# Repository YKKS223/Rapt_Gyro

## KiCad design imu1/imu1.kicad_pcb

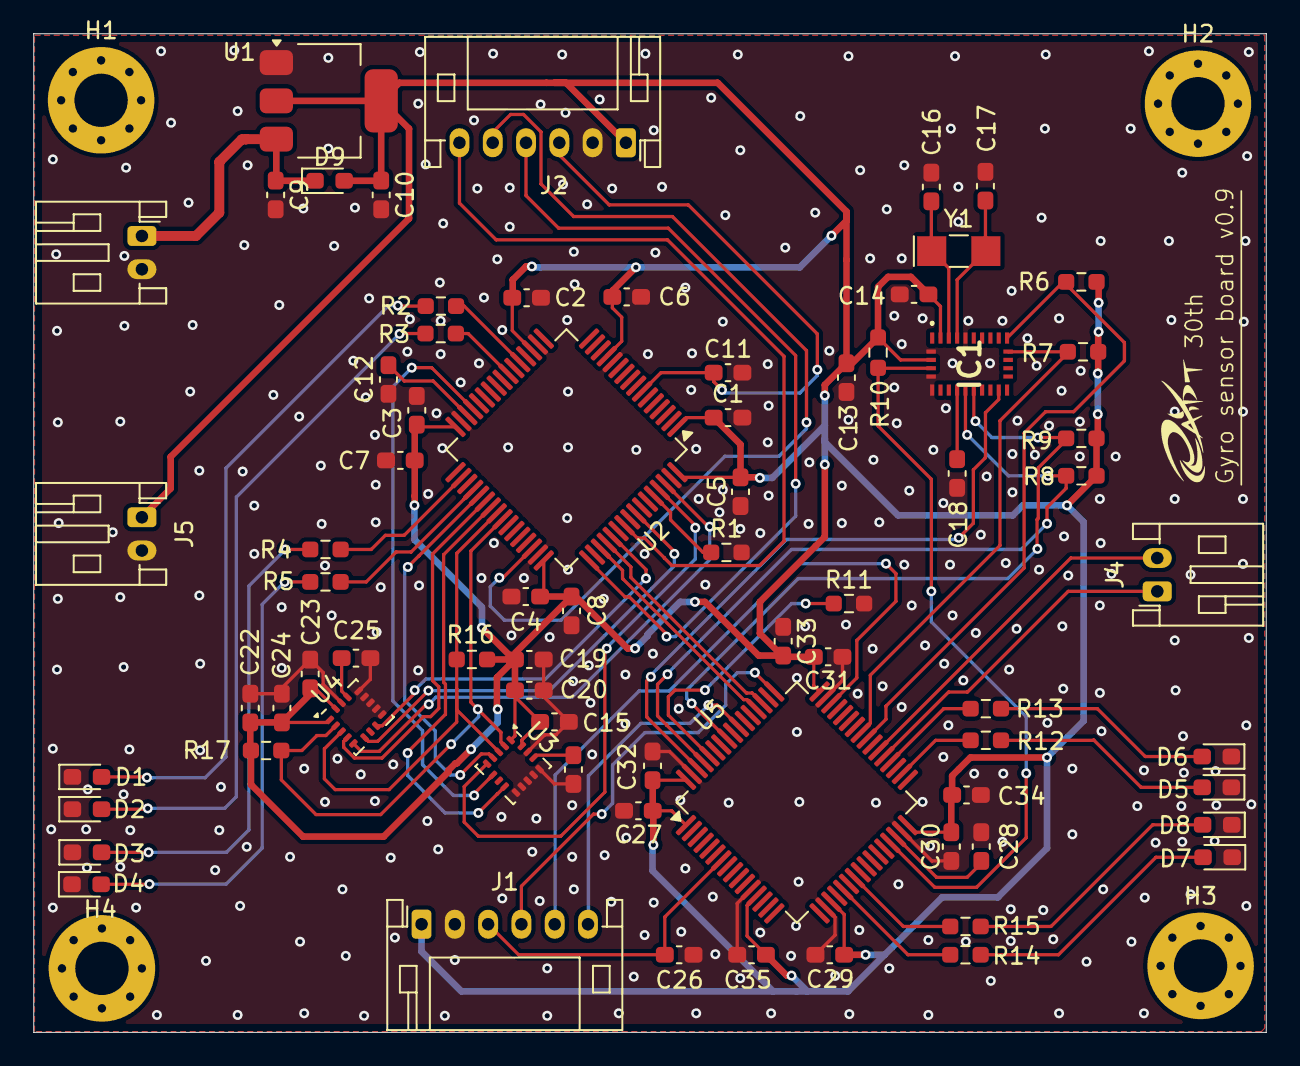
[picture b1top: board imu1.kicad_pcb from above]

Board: 2 copper layers, 74.0 x 60.0 mm, 77 parts (0 on the bottom side), 56 nets.

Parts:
C1, C12, C27, C28: 4.7uC; C_0603_1608Metric_Pad1.08x0.95mm_HandSolder
C2, C3, C4, C5, C6, C7, C8, C11, C13, C14, C18, C19, C21, C22, C25, C26, C29, C30, C31, C32, C33, C34, C35: 0.1uC; C_0603_1608Metric_Pad1.08x0.95mm_HandSolder
C9, C10: 10uC; C_0603_1608Metric_Pad1.08x0.95mm_HandSolder
C15, C23: 2.2uC; C_0603_1608Metric_Pad1.08x0.95mm_HandSolder
C16, C17: 22pC; C_0603_1608Metric_Pad1.08x0.95mm_HandSolder
C20, C24: 10nC; C_0603_1608Metric_Pad1.08x0.95mm_HandSolder
D1, D2, D3, D4, D5, D6, D7, D8: IR26; D_0603_1608Metric_Pad1.05x0.95mm_HandSolder
D9: D; D_0603_1608Metric_Pad1.05x0.95mm_HandSolder
H1, H2, H3, H4: MountingHole_Pad; MountingHole_3.2mm_M3_Pad_Via
IC1: BNO085
J1, J2: Conn_01x06_Pin; JST_PH_S6B-PH-K_1x06_P2.00mm_Horizontal
J3: Power; JST_PH_S2B-PH-K_1x02_P2.00mm_Horizontal
J4: UART0; JST_PH_S2B-PH-K_1x02_P2.00mm_Horizontal
J5: 3.3v; JST_PH_S2B-PH-K_1x02_P2.00mm_Horizontal
R1, R8, R9, R10, R11: 10kR; R_0603_1608Metric_Pad0.98x0.95mm_HandSolder
R2, R3, R4, R5, R12, R13, R14, R15: 1kR; R_0603_1608Metric_Pad0.98x0.95mm_HandSolder
R6, R7, R16, R17: 2.2kR; R_0603_1608Metric_Pad0.98x0.95mm_HandSolder
U1: Regulator; SOT-223-3_TabPin2
U2, U5: STM32F446RETx; LQFP-64_10x10mm_P0.5mm
U3, U4: ICM-20602; LGA-16_3x3mm_P0.5mm_LayoutBorder3x5y
Y1: 32.768KHZ; Crystal_SMD_MicroCrystal_CC7V-T1A-2Pin_3.2x1.5mm_HandSolder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

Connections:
+3.3V: C1.1, C2.2, C3.2, C4.2, C5.2, C6.2, C7.2, C8.2, C10.1, C13.2, C14.2, C15.1, C19.1, C20.1, C22.1, C23.1, C24.2, C27.1, C29.2, C30.2, C31.2, C32.2, C33.2, C34.2, C35.2, D9.2 (A), IC1.3 (VDD), IC1.28 (VDDIO), J1.1, J2.1, J5.1, R6.1, R7.1, R8.1, R9.1, R10.1, R16.1, R17.1, U1.2 (VO), U2.1 (VBAT), U2.13 (VDDA), U2.19 (VDD), U2.32 (VDD), U2.48 (VDD), U2.64 (VDD), U3.1 (VDDIO), U3.16 (VDD), U4.1 (VDDIO), U4.16 (VDD), U5.1 (VBAT), U5.13 (VDDA), U5.19 (VDD), U5.32 (VDD), U5.48 (VDD), U5.64 (VDD)
AD0_1: U2.37 (PC6), U3.4 (SAO/SD0)
AD0_2: U2.38 (PC7), U4.4 (SAO/SD0)
BOOTN: IC1.4 (BOOTN), R10.2, U5.29 (PB10)
CLKSEL: IC1.10 (CLKSEL0), R8.2, U5.61 (PB8)
CS: U2.61 (PB8), U3.5 (~CS)
CS1: U2.62 (PB9), U4.5 (~CS)
FSYNC: U2.39 (PC8), U3.8 (FSYNC)
FSYNC1: U2.53 (PC12), U4.8 (FSYNC)
GND: C1.2, C2.1, C3.1, C4.1, C5.1, C6.1, C7.1, C8.1, C9.2, C10.2, C11.2, C12.2, C13.1, C14.1, C15.2, C16.1, C17.1, C18.2, C19.2, C20.2, C21.2, C22.2, C23.2, C24.1, C25.2, C26.2, C27.2, C28.2, C29.1, C30.1, C31.1, C32.1, C33.1, C34.1, C35.1, D1.1 (K), D2.1 (K), D3.1 (K), D4.1 (K), D5.1 (K), D6.1 (K), D7.1 (K), D8.1 (K), IC1.2 (GND_1), IC1.5 (PS1), IC1.6 (PS0/WAKE), IC1.25 (GND_2), J1.2, J2.2, J3.2, J5.2, R1.2, R11.2, U1.1 (GND), U2.12 (VSSA), U2.18 (VSS), U2.31 (VSS), U2.47 (VSS), U2.63 (VSS), U3.9 (GND), U3.10 (GND), U3.11 (GND), U3.12 (GND), U3.13 (GND), U3.15 (GND), U4.9 (GND), U4.10 (GND), U4.11 (GND), U4.12 (GND), U4.13 (GND), U4.15 (GND), U5.12 (VSSA), U5.18 (VSS), U5.31 (VSS), U5.47 (VSS), U5.63 (VSS)
INT: IC1.14 (H_INTN), U5.62 (PB9)
INT1: U2.29 (PB10), U3.6 (INT)
INT2: U2.57 (PB5), U4.6 (INT)
unnamed: D1.2 (A), R2.1
unnamed: D2.2 (A), R3.1
unnamed: D3.2 (A), R4.1
unnamed: D4.2 (A), R5.1
unnamed: D5.2 (A), R12.1
unnamed: D6.2 (A), R13.1
unnamed: D7.2 (A), R14.1
unnamed: D8.2 (A), R15.1
unnamed: C18.1, IC1.9 (CAP)
unnamed: C16.2, IC1.27 (XIN32), Y1.1
unnamed: C17.2, IC1.26 (XOUT32/CLKSEL1), Y1.2
unnamed: R1.1, U2.60 (BOOT0)
unnamed: R2.2, U2.21 (PA5)
unnamed: R3.2, U2.23 (PA7)
unnamed: R4.2, U2.34 (PB13)
unnamed: R5.2, U2.36 (PB15)
unnamed: C12.1, U2.30 (VCAP_1)
unnamed: C21.1, U3.14 (REGOUT)
unnamed: C25.1, U4.14 (REGOUT)
unnamed: R11.1, U5.60 (BOOT0)
unnamed: R14.2, U5.21 (PA5)
unnamed: R15.2, U5.23 (PA7)
unnamed: R12.2, U5.34 (PB13)
unnamed: R13.2, U5.36 (PB15)
unnamed: C28.1, U5.30 (VCAP_1)
RST: IC1.11 (NRST), R9.2, U5.57 (PB5)
RX: U2.51 (PC10), U5.52 (PC11)
RX1: J4.2, U5.38 (PC7)
SCL: IC1.19 (H_SCL/SCK/RX), R7.2, U5.41 (PA8)
SCL1: R17.2, U2.41 (PA8), U3.2 (SCL/SPC), U4.2 (SCL/SPC)
SDA: IC1.20 (H_SDA/H_MISO/TX_), R6.2, U5.40 (PC9)
SDA1: R16.2, U2.40 (PC9), U3.3 (SDA/SDI), U4.3 (SDA/SDI)
STL-3: C26.1, J1.3, U5.7 (NRST)
STL-3_1: C11.1, J2.3, U2.7 (NRST)
STL-4: J1.4, U5.49 (PA14)
STL-4_1: J2.4, U2.49 (PA14)
STL-5: J1.5, U5.46 (PA13)
STL-5_1: J2.5, U2.46 (PA13)
STL-6: J1.6, U5.55 (PB3)
STL-6_1: J2.6, U2.55 (PB3)
TX: U2.52 (PC11), U5.51 (PC10)
TX1: J4.1, U5.37 (PC6)
VCC: C9.1, D9.1 (K), J3.1, U1.3 (VI)

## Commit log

2025-01-14 V0.9保存
